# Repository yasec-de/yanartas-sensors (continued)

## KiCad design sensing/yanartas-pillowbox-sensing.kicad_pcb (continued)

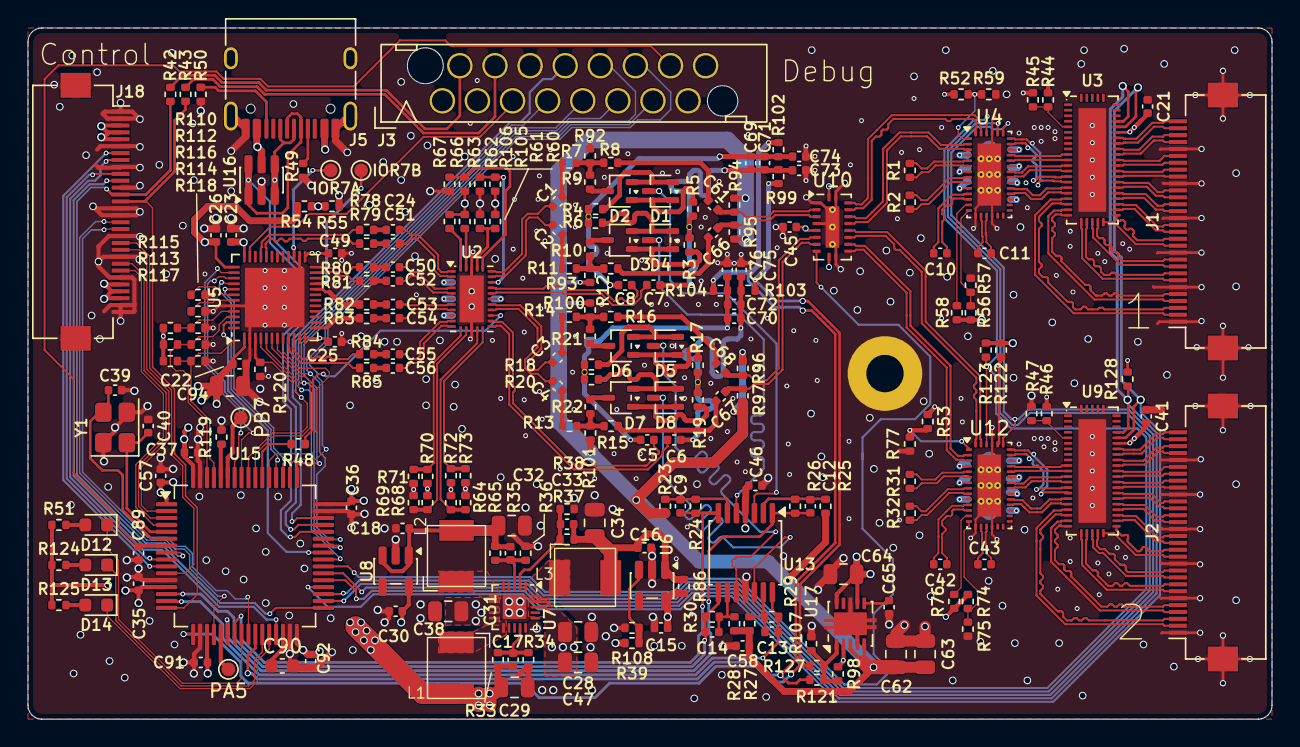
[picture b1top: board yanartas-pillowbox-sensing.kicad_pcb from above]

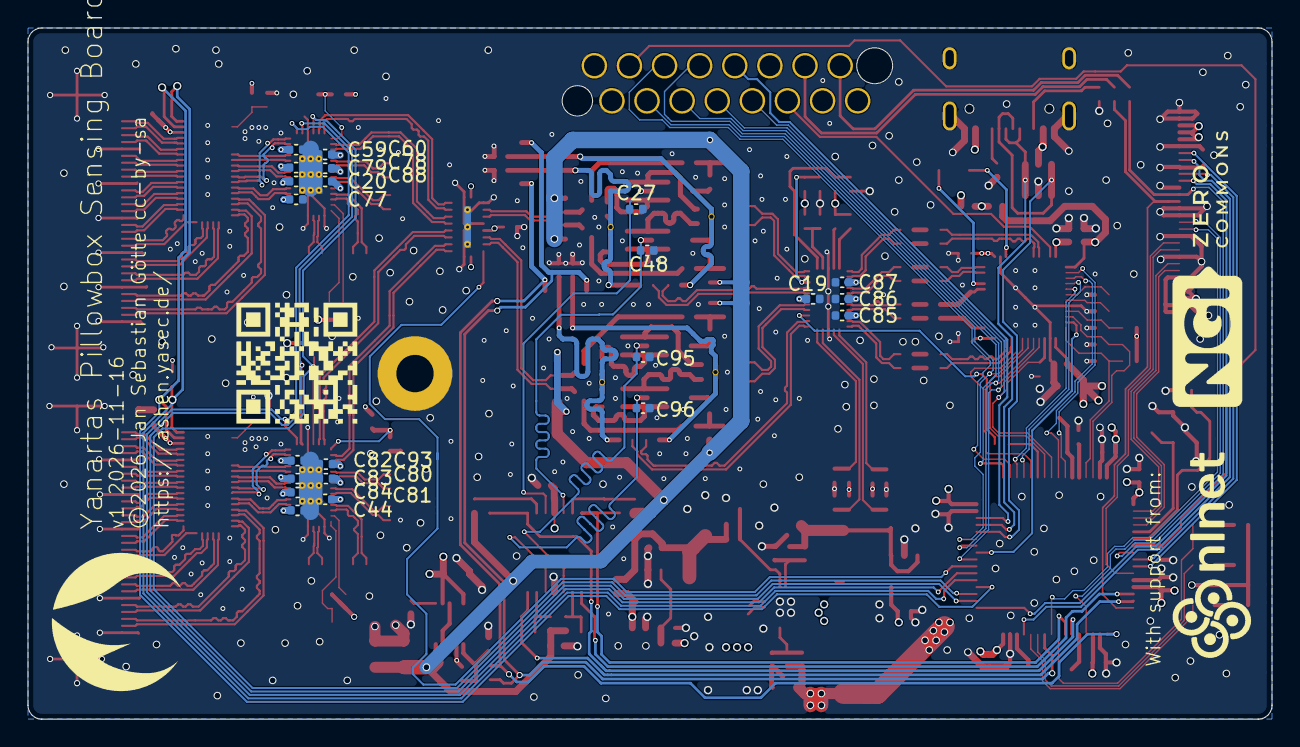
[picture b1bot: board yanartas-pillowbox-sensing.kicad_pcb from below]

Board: 4 copper layers, 90.0 x 50.0 mm, 261 parts (30 on the bottom side), 270 nets.

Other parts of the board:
ashen-logo_w10.00mm: G*****; ashen-logo_w10.00mm
kobee-studio-6AF9AA16: Kobee Studio; kobee-studio-6AF9AA16
ngi-zero-commons-logo_w20.00mm: G*****; ngi-zero-commons-logo_w20.00mm
nlnet-logo_w15.00mm: G*****; nlnet-logo_w15.00mm

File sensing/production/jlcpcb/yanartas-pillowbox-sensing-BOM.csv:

Comment,Designator,Footprint,LCSC Part #
220n,"C1,C2,C3,C4,C5,C6,C7,C8,C10,C11,C24,C42,C43,C50,C51,C52,C53,C54,C55,C56,C61,C65,C66,C67,C68,C71,C72,C73,C74,C75,C76",C_0402_1005Metric,C16772
1u,"C15,C16,C18,C19,C20,C21,C22,C23,C25,C26,C30,C35,C36,C37,C41,C44,C45,C46,C49,C57,C58,C59,C60,C77,C78,C79,C80,C81,C82,C83,C84,C85,C86,C87,C88,C91,C92,C93",C_0402_1005Metric,C52923
22p,"C17,C31,C33",C_0402_1005Metric,C1555
10p,"C27,C39,C40,C48,C95,C96",C_0402_1005Metric,C32949
22u/10V,"C28,C38,C47",C_0805_2012Metric,C45783
22u/6V3,"C29,C32,C34,C62,C63,C64,C94",C_0805_2012Metric,C45783
1n,"C69,C70",C_0402_1005Metric,C1523
100n,C89,C_0402_1005Metric,C1525
4u7/10V,C90,C_0603_1608Metric,C19666
BAT15-04W,"D1,D2,D3,D4,D5,D6,D7,D8",SOT-323_SC-70,C5380972
LED,"D12,D13,D14",LED_0603_1608Metric,C2290
FH12S-30S-0.5SH(55),"J1,J2,J18",Hirose_FH12-30S-0.5SH_1x30-1MP_P0.50mm_Horizontal,C3169607
2u2,"L1,L2,L3",CJIANG_FXL0420,C167206
100,"R1,R2,R31,R32,R42,R43",R_0402_1005Metric,C25076
91,"R3,R4,R5,R6,R17,R18,R19,R20",R_0402_1005Metric,C270574
16,"R7,R8,R9,R10,R11,R12,R13,R14,R15,R16,R21,R22",R_0402_1005Metric,C227309
1k,"R23,R25,R27,R28,R51,R99,R102,R103,R104,R110,R112,R124,R125",R_0402_1005Metric,C11702
3k3,"R24,R26,R29,R30",R_0402_1005Metric,C25890
100k,"R33,R35,R37,R48",R_0402_1005Metric,C25741
22k1,"R34,R39",R_0402_1005Metric,C43473
18k2,R36,R_0402_1005Metric,C25859
49k9,R38,R_0402_1005Metric,C25897
10k,"R44,R46,R56,R58,R59,R74,R76,R77,R92,R93,R94,R95,R96,R97,R100,R101,R108,R119,R121,R127,R128",R_0402_1005Metric,C25744
5k1,"R49,R50",R_0402_1005Metric,C25905
0,R54,R_0402_1005Metric,C17168
4k7,"R66,R69,R73,R105,R106,R113,R115,R117,R120",R_0402_1005Metric,C25900
10,"R78,R79,R80,R81,R82,R83,R84,R85",R_0402_1005Metric,C25077
470k,"R98,R107",R_0402_1005Metric,C25790
3k9,"R122,R123",R_0402_1005Metric,C51721
PI3HDX12311,U2,Diodes_XEA32_X1-QFN-32-1EP_2.85x4.5mm_P0.4mm_EP1.75x3.4mm,C49454029
PI3WVR41310,"U3,U9",Diodes_ZL52_TQFN-52-1EP_3.5x9mm_P0.4mm_EP2x7.5mm,
TMUXHS4446,"U4,U12",Texas_WQFN-40-1EP_3x6mm_P0.4mm_EP1.7x4.5mm_ThermalVias,C35471229
GW1NZ-LV1QN48C6,U5,Gowin_QN48_QFN-48-1EP_6x6mm_P0.4mm_EP4.3x4.3mm,C5799569
TLV74312PDBVR,U6,SOT-23-5,C485149
TMI7003C,U7,QFN-20-1EP_3x3mm_P0.4mm_EP1.7x1.7mm,C840566
TLV74333PDBVR,U8,SOT-23-5,C51953291
TMUXHS4212,U10,Texas_RKS0020A_VQFN-20-1EP_2.5x4.5mm_P0.5mm_EP1x3mm_ThermalVias,C2869871
OPA4354,U13,TSSOP-14_4.4x5mm_P0.65mm,C527494
STM32U575RGTx,U15,LQFP-64_10x10mm_P0.5mm,C5270980
USBLC6-4SC6,U16,SOT-23-6,C558419
TPS51200DRC,U17,VSON-10-1EP_3x3mm_P0.5mm_EP1.65x2.4mm,C34771
16MHz 10p,Y1,Crystal_SMD_3225-4Pin_3.2x2.5mm,C13738

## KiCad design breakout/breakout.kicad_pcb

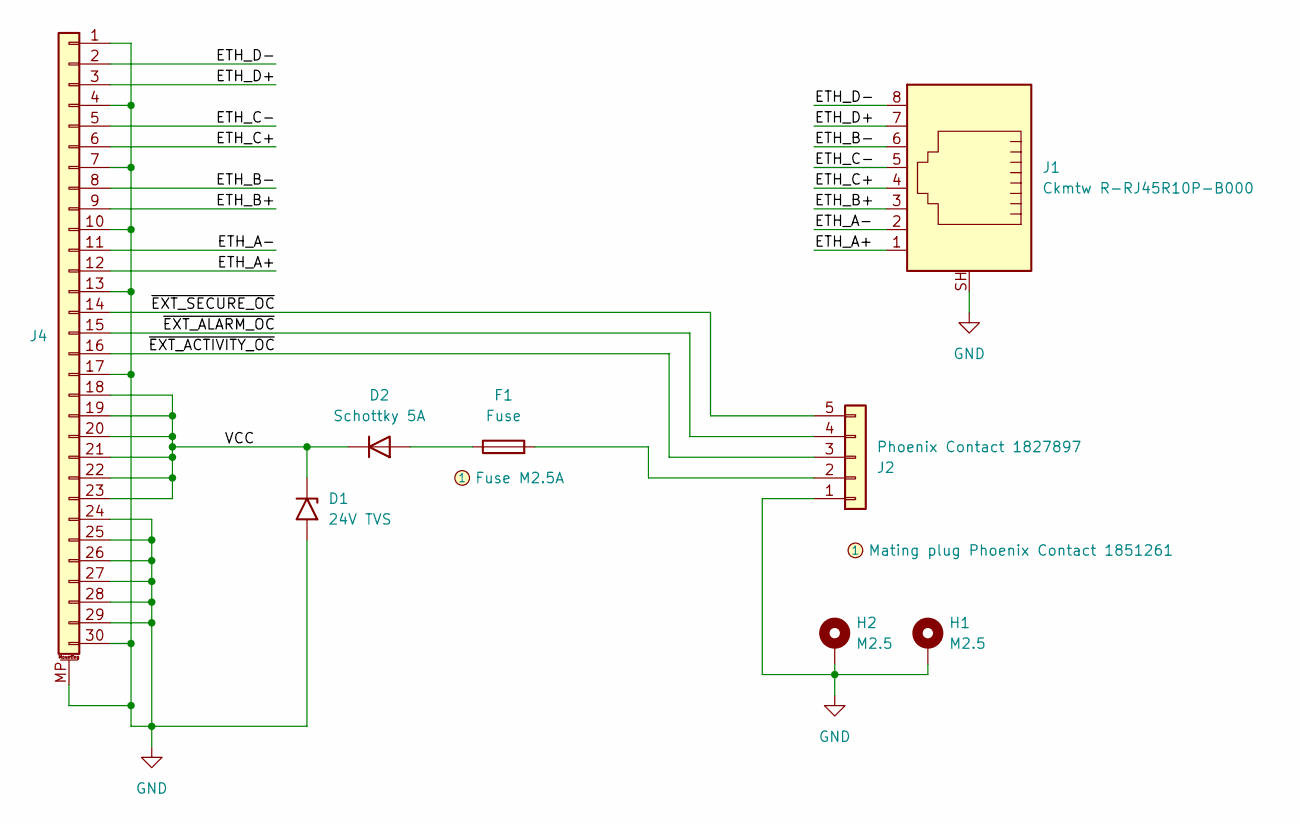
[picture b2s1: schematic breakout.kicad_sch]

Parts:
D1: 24V TVS; D_DO-27_P15.24mm_Horizontal; LCSC C5350009
D2: Schottky 5A; D_DO-27_P15.24mm_Horizontal; LCSC C154825
F1: Fuse; Fuseholder_Clip-5x20mm_Littelfuse_520_Inline_P20.50x5.80mm_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; LCSC C142924
H1, H2: M2.5; MountingHole_2.7mm_M2.5_DIN965_Pad_TopBottom
J1: Ckmtw R-RJ45R10P-B000; RJ45_Ninigi_GE; LCSC C386758
J2: Phoenix Contact 1827897; PhoenixContact_MC_1,5_5-GF-3.81_1x05_P3.81mm_Horizontal_Thr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; LCSC C3579871
J4: FH12S-30S-0.5SH(55); Hirose_FH12-30S-0.5SH_1x30-1MP_P0.50mm_Horizontal; LCSC C3169607

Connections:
/ETH_A+: J1.1, J4.12
/ETH_A-: J1.2, J4.11
/ETH_B+: J1.3, J4.9
/ETH_B-: J1.6, J4.8
/ETH_C+: J1.4, J4.6
/ETH_C-: J1.5, J4.5
/ETH_D+: J1.7, J4.3
/ETH_D-: J1.8, J4.2
/VCC: D1.1 (A1), D2.1 (K), J4.18, J4.19, J4.20, J4.21, J4.22, J4.23
/~EXT_ACTIVITY_OC: J2.3, J4.16
/~EXT_ALARM_OC: J2.4, J4.15
/~EXT_SECURE_OC: J2.5, J4.14
GND: D1.2 (A2), H1.1 (1_1), H2.1 (1_1), J1.SH, J2.1, J4.1, J4.4, J4.7, J4.10, J4.13, J4.17, J4.24, J4.25, J4.26, J4.27, J4.28, J4.29, J4.30, J4.MP (MountPin)
unnamed: D2.2 (A), F1.1
unnamed: F1.2, J2.2

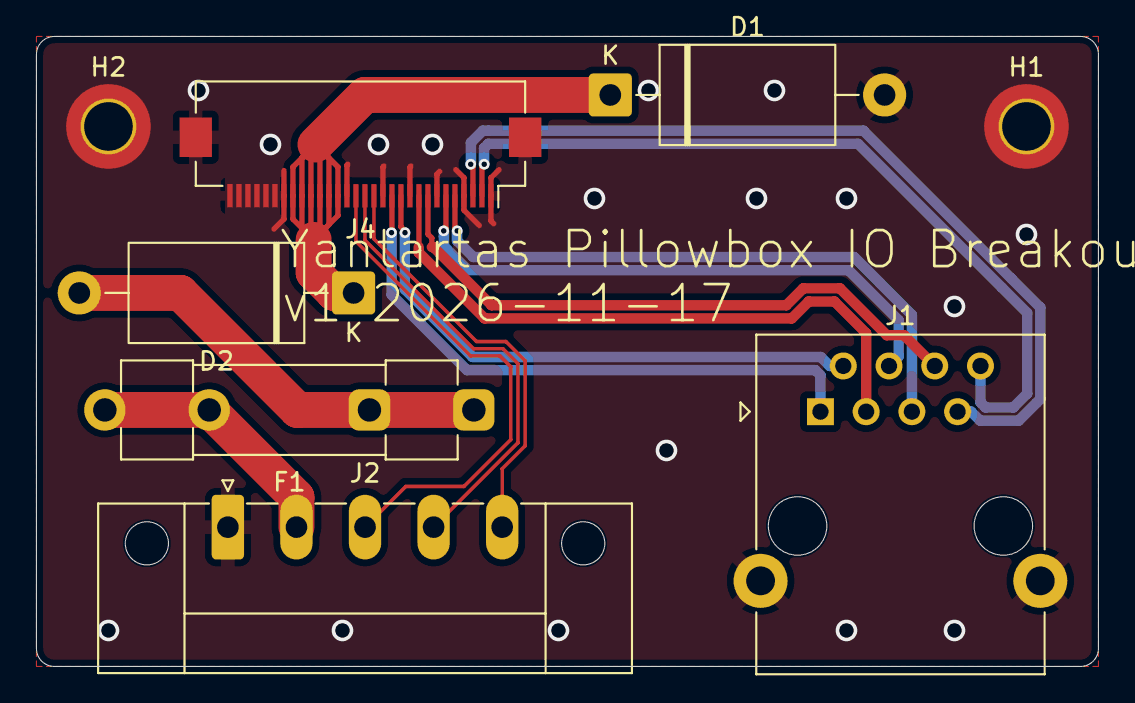
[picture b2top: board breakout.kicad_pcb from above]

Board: 2 copper layers, 59.0 x 35.0 mm, 8 parts (0 on the bottom side), 15 nets.

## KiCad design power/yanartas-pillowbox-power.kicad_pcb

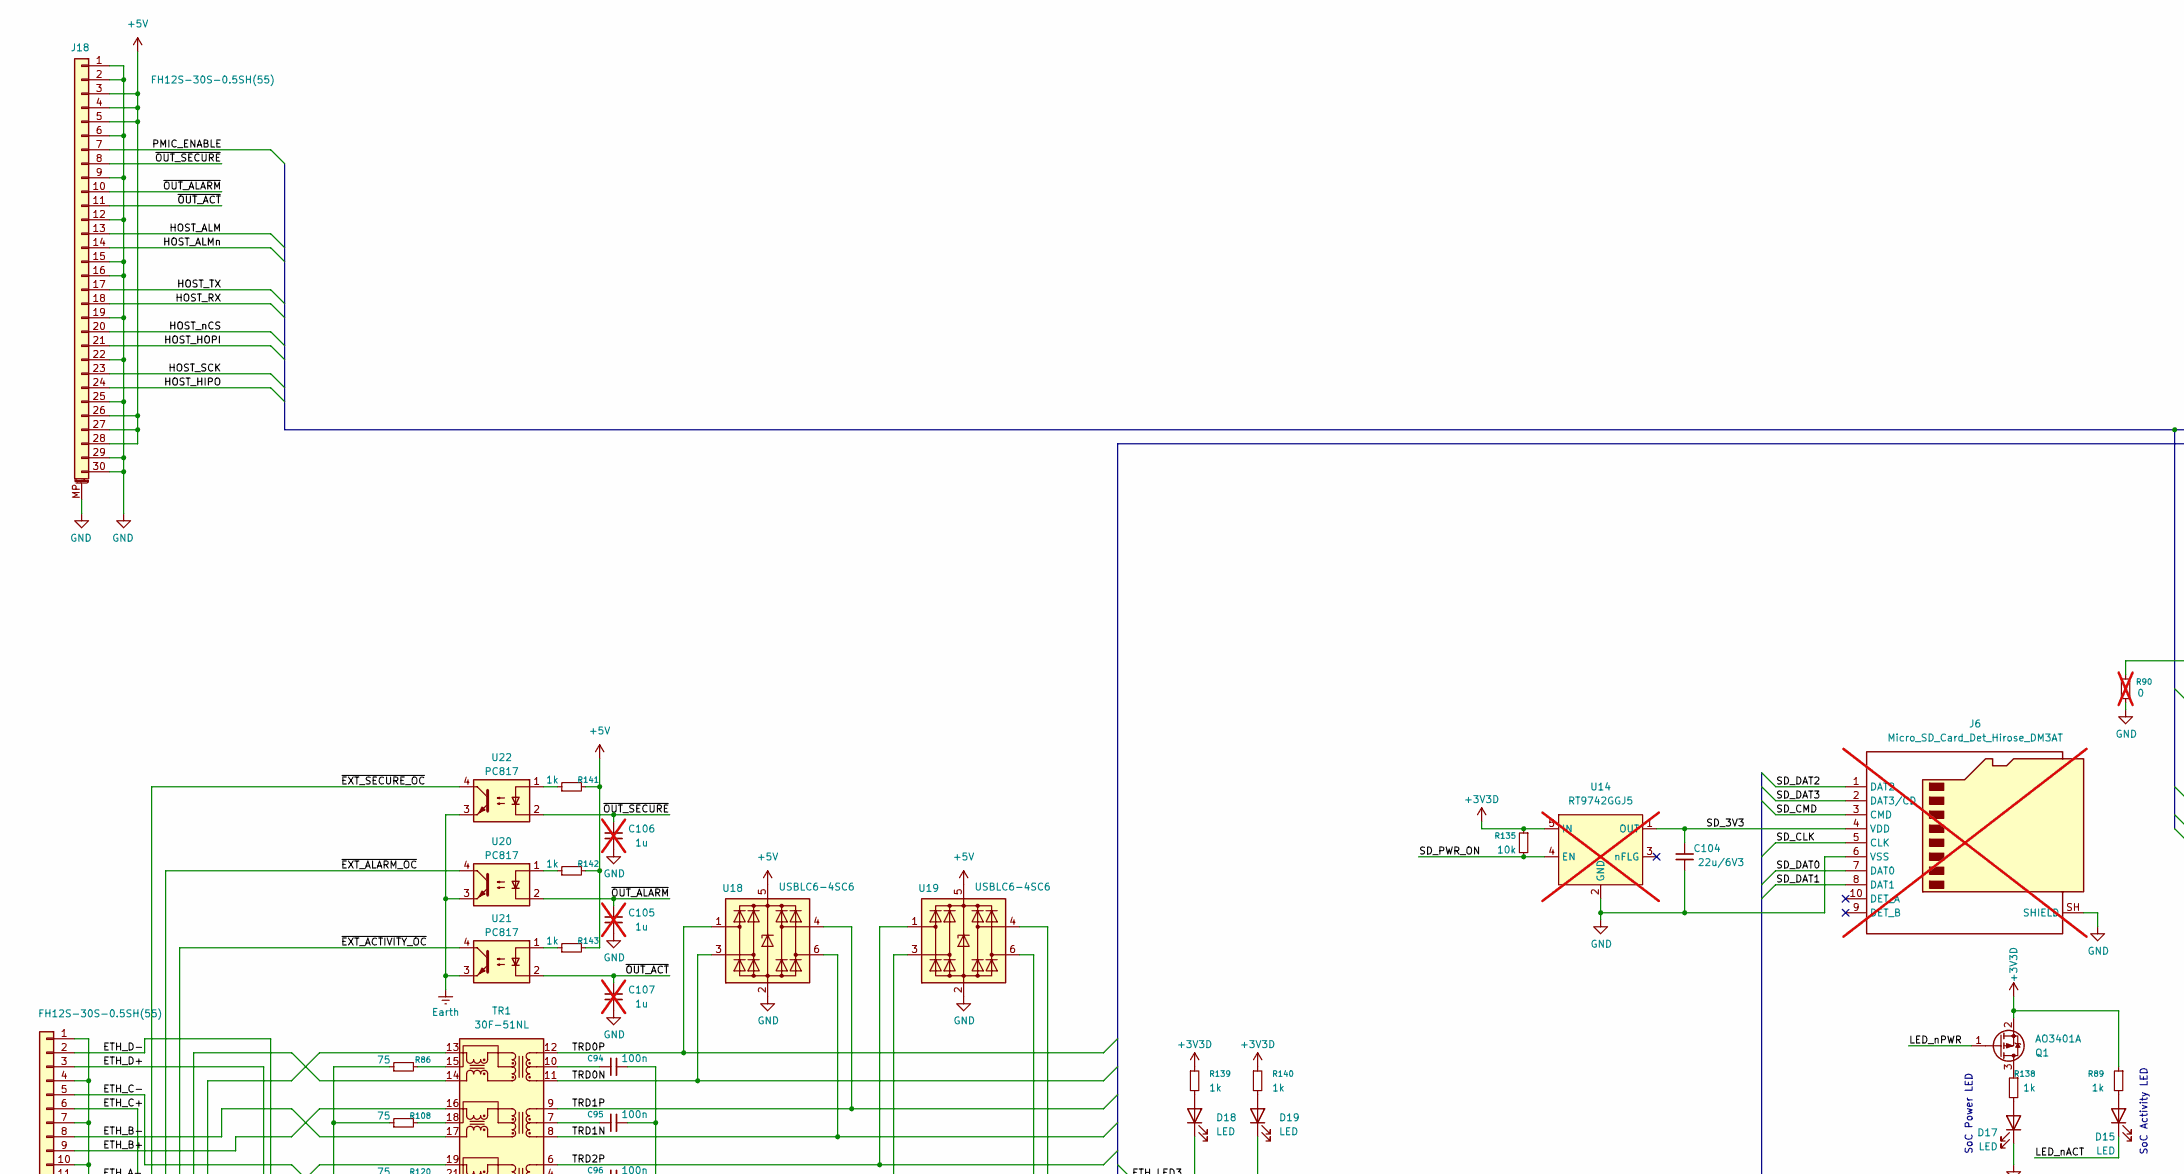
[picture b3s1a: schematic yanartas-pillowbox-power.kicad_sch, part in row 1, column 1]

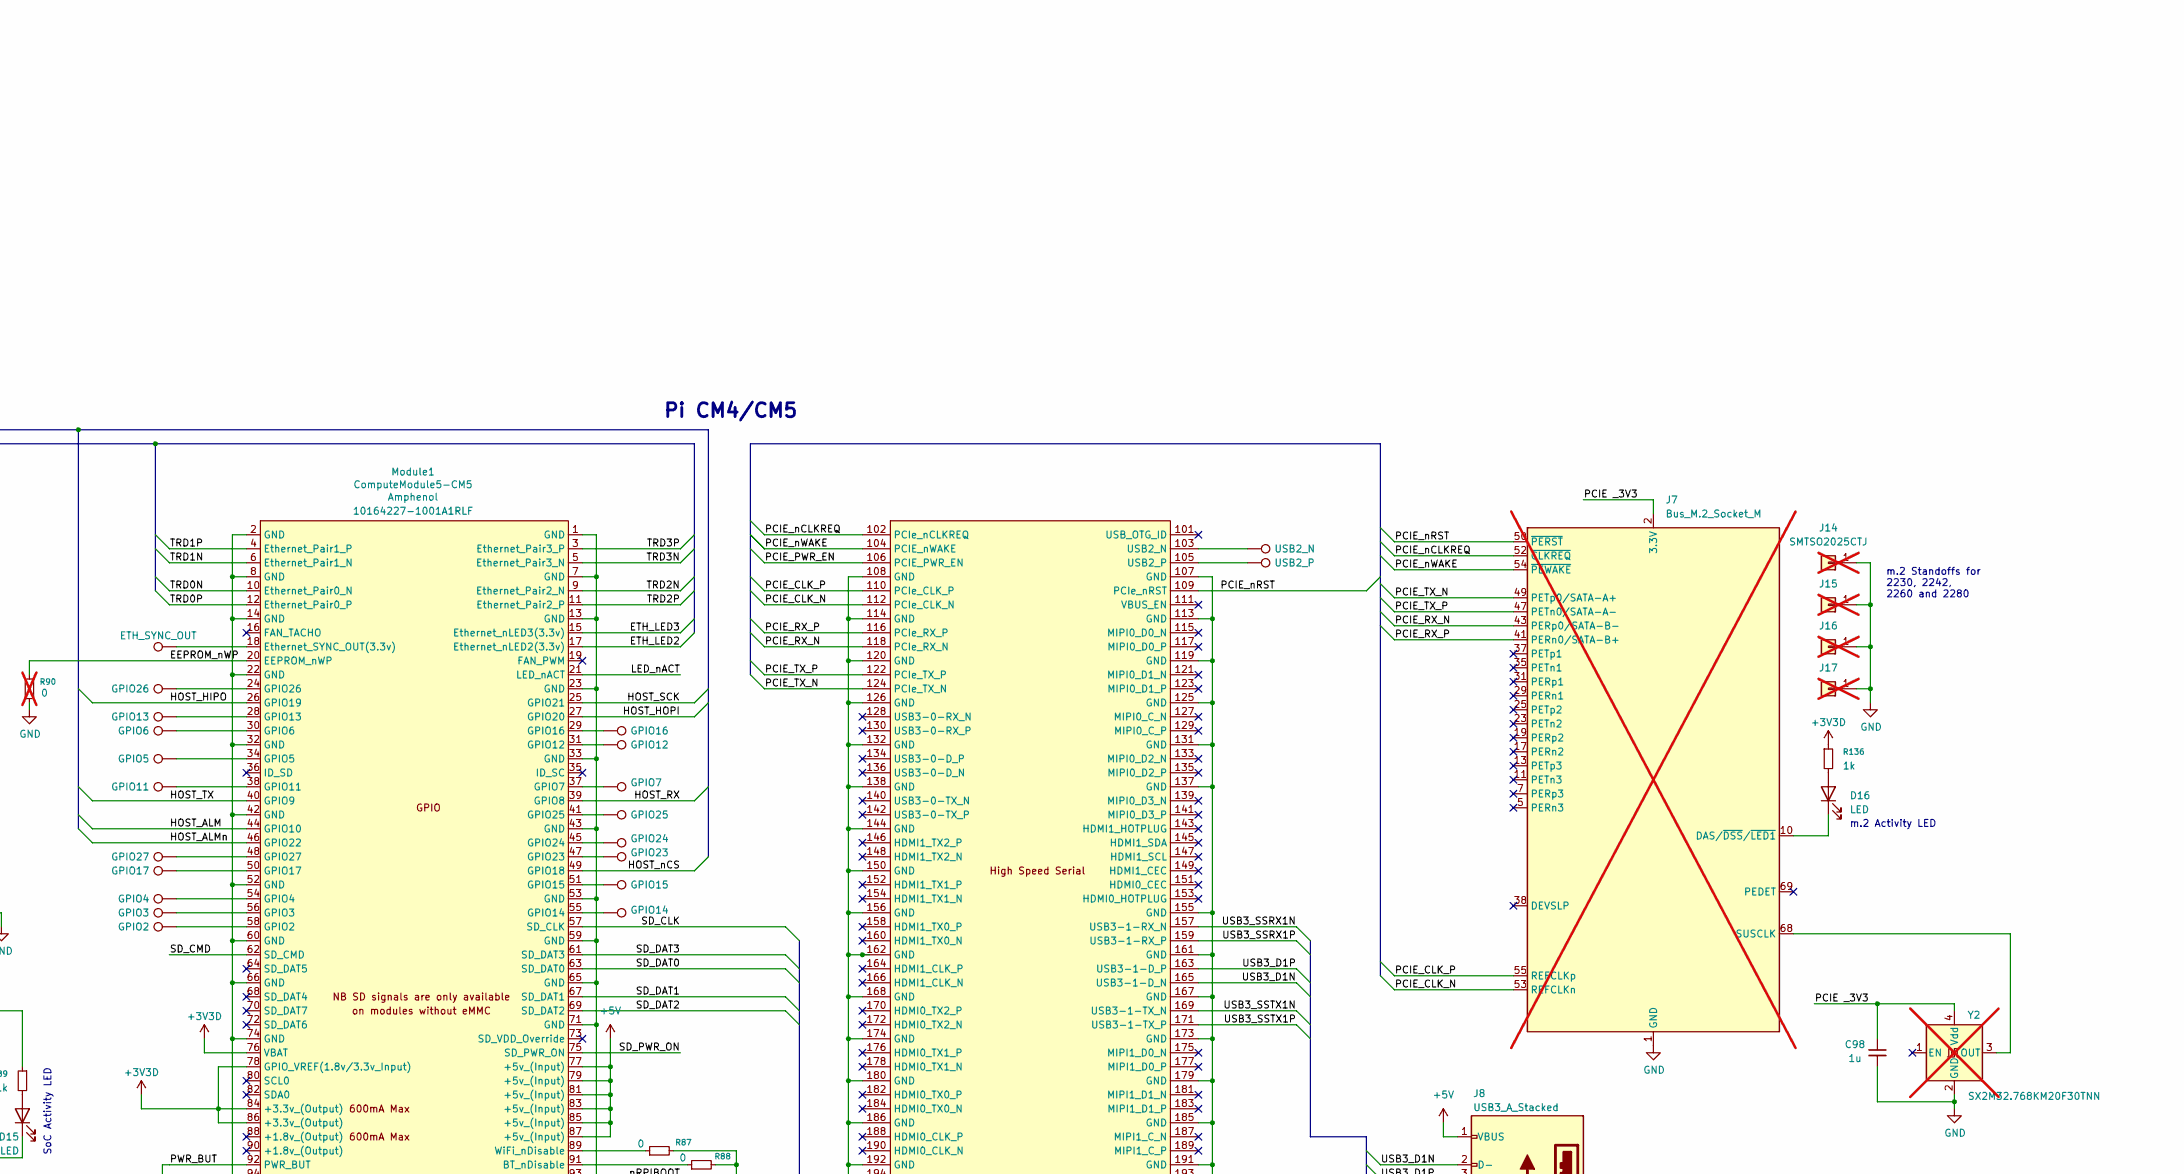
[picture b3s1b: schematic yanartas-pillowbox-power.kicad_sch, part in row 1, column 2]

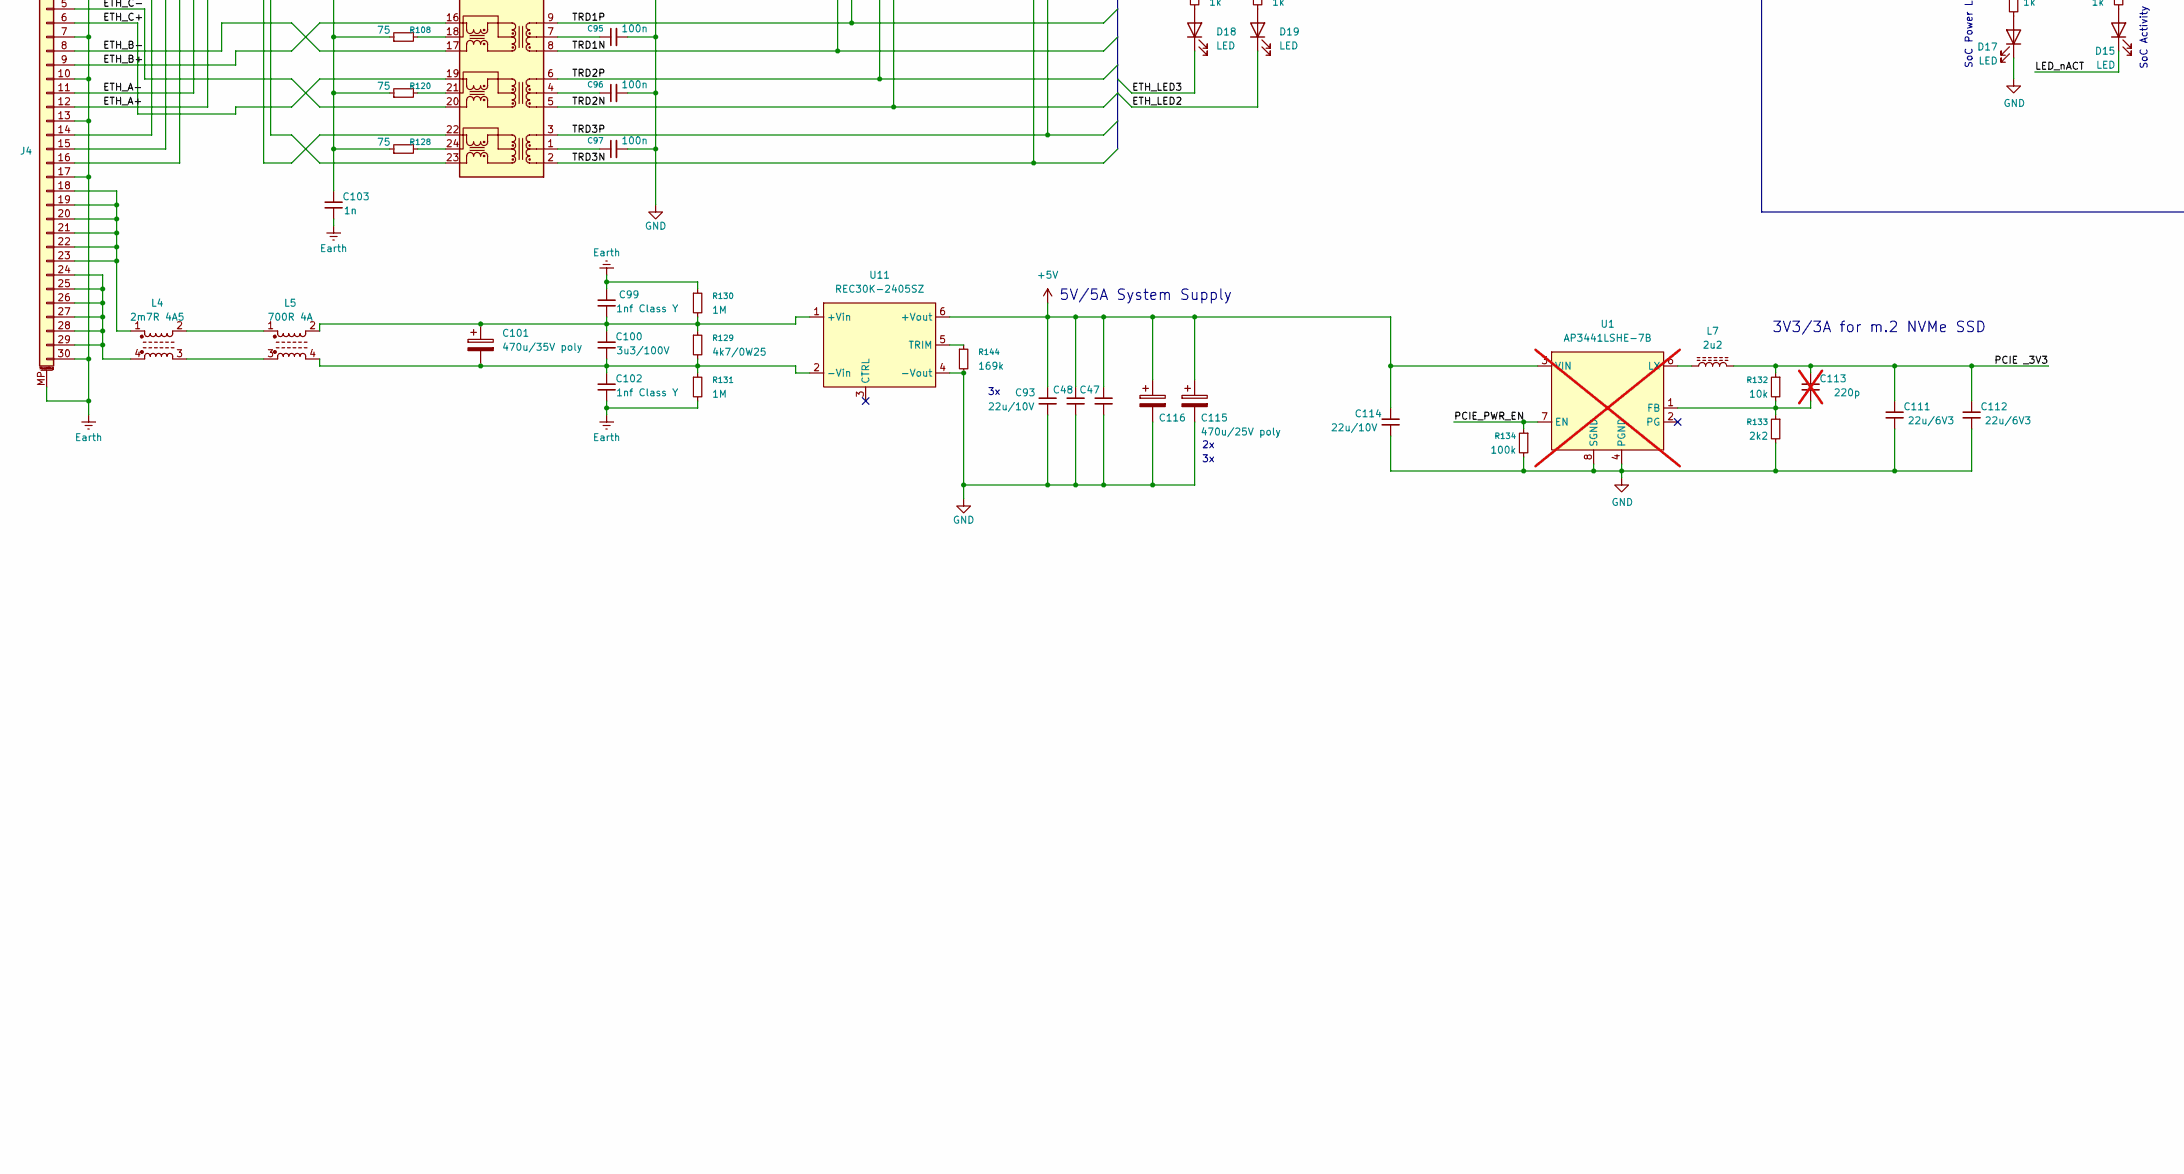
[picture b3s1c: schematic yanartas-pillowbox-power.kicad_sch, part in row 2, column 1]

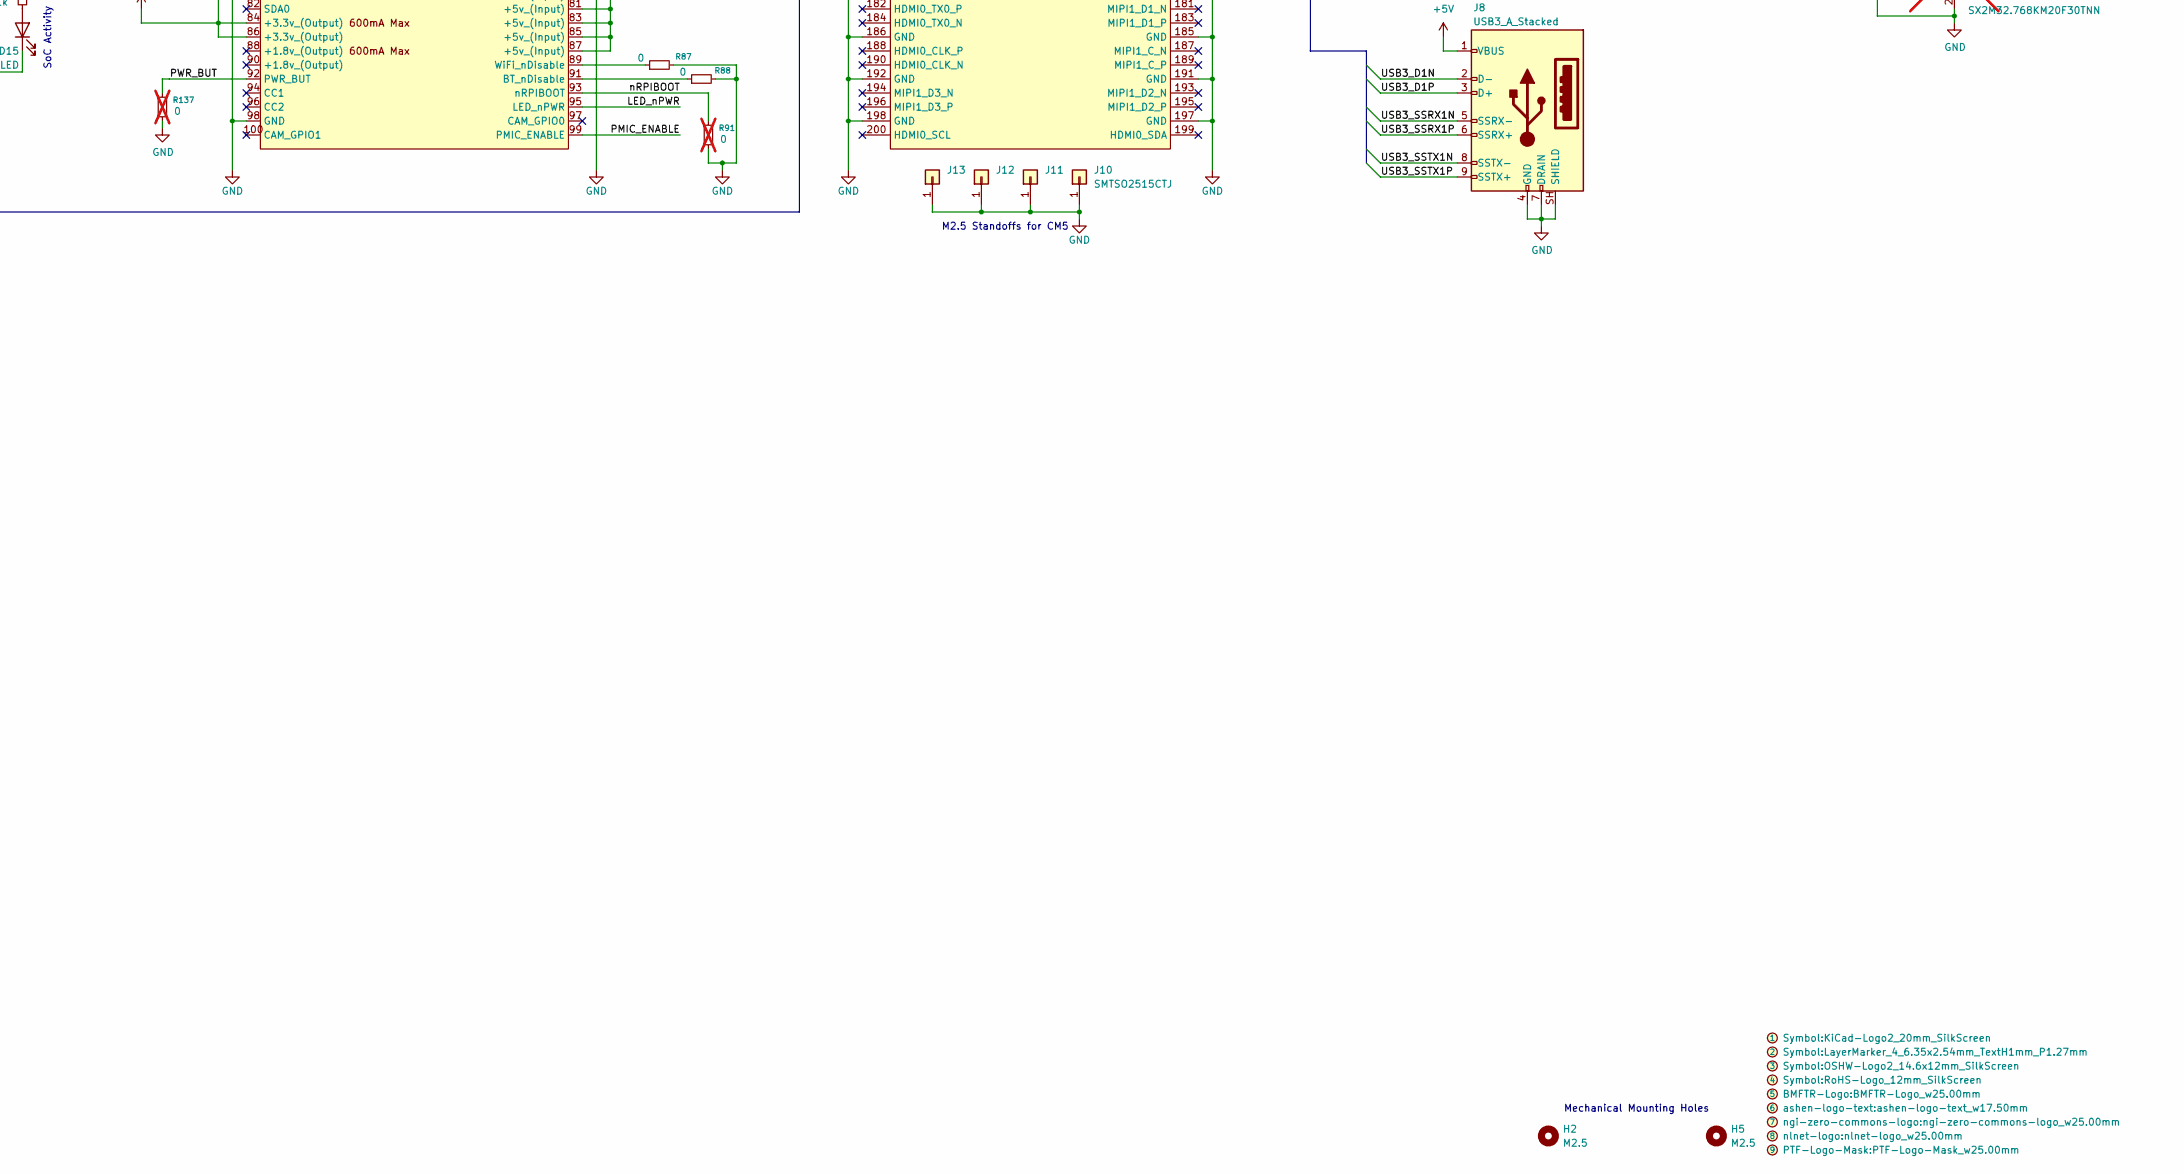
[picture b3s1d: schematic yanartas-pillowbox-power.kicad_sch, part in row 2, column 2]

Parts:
C47, C48, C93, C114: 22u/10V; C_0805_2012Metric; LCSC C45783
C94, C95, C96, C97: 100n; C_0402_1005Metric; LCSC C1525
C98: 1u; C_0402_1005Metric; LCSC C52923
C99, C102: 1nf Class Y; C_Rect_L13.0mm_W4.0mm_P10.00mm_FKS3_FKP3_MKS4; LCSC C361361
C100: 3u3/100V; C_1206_3216Metric; LCSC C695361
C101: 470u/35V poly; CP_Radial_D10.0mm_P5.00mm; MfgPN A750MV477M1VAAE018; LCSC C1020051
C103: 1n; C_0603_1608Metric; LCSC C1588
C104, C111, C112: 22u/6V3; C_0805_2012Metric; LCSC C45783
C105, C106, C107: 1u; C_0402_1005Metric; LCSC C52923; not fitted
C113: 220p; C_0402_1005Metric; not fitted
C115, C116: 470u/25V poly; CP_Radial_D10.0mm_P5.00mm; MfgPN A750MS477M1EAAE015; LCSC C696345
D15, D16, D17, D18, D19: LED; LED_0603_1608Metric; LCSC C2290
H2, H5: M2.5; MountingHole_2.7mm_M2.5; LCSC NA
J4, J18: FH12S-30S-0.5SH(55); Hirose_FH12-30S-0.5SH_1x30-1MP_P0.50mm_Horizontal; LCSC C3169607
J6: Micro_SD_Card_Det_Hirose_DM3AT; microSD_HC_Hirose_DM3AT-SF-PEJM5; MPN DM3AT-SF-PEJM5; LCSC C114218; not fitted
J7: Bus_M.2_Socket_M; CONN-SMD_MDT420M02001; LCSC C2927698; not fitted
J8: USB3_A_Stacked; USB_A_Receptacle_XKB_U231-091N-4BLRA00-S; LCSC C2880618
J10, J11, J12, J13: SMTSO2515CTJ; SINHOO_SMTSO25XX; LCSC C2915629
J14, J15, J16, J17: SMTSO2025CTJ; SINHOO_SMTSO20XX; LCSC C2916321; not fitted
L4: 2m7R 4A5; EPCOS_B82723A; MPN B82723A2402N001; LCSC NA
L5: 700R 4A; TDK_ACM7060; MPN ACM7060-701-2PL-TL01; LCSC C78246
L7: 2u2; CJIANG_FXL0420; LCSC C167206
Module1: ComputeModule5-CM5; Raspberry-Pi-5-Compute-Module-A; Part Description 100 Position Connector Receptacle, Cent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; LCSC C6782225
Module2: ComputeModule5-CM5; Raspberry-Pi-5-Compute-Module-B; Part Description 100 Position Connector Receptacle, Cent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; LCSC C6782225
Q1: AO3401A; SOT-23; LCSC C15127
R86, R108, R120, R128: 75; R_0402_1005Metric; LCSC C25133
R87, R88: 0; R_0402_1005Metric; LCSC C17168
R89, R136, R138, R139, R140, R141, R142, R143: 1k; R_0402_1005Metric; LCSC C11702
R90, R91, R137: 0; R_0402_1005Metric; LCSC C17168; not fitted
R129: 4k7/0W25; R_1206_3216Metric; LCSC C17936
R130, R131: 1M; R_0603_1608Metric; LCSC C22935
R132, R135: 10k; R_0402_1005Metric; LCSC C25744
R133: 2k2; R_0402_1005Metric; LCSC C25879
R134: 100k; R_0402_1005Metric; LCSC C25741
R144: 169k; R_0603_1608Metric; LCSC C22817
TP1: GPIO27; TestPoint_Pad_D1.0mm; LCSC NA
TP2: GPIO17; TestPoint_Pad_D1.0mm; LCSC NA
TP3: GPIO4; TestPoint_Pad_D1.0mm; LCSC NA
TP4: GPIO3; TestPoint_Pad_D1.0mm; LCSC NA
TP5: GPIO2; TestPoint_Pad_D1.0mm; LCSC NA
TP6: GPIO11; TestPoint_Pad_D1.0mm; LCSC NA
TP7: GPIO5; TestPoint_Pad_D1.0mm; LCSC NA
TP8: GPIO6; TestPoint_Pad_D1.0mm; LCSC NA
TP9: GPIO13; TestPoint_Pad_D1.0mm; LCSC NA
TP10: GPIO26; TestPoint_Pad_D1.0mm; LCSC NA
TP11: ETH_SYNC_OUT; TestPoint_Pad_D1.0mm; LCSC NA
TP12: GPIO14; TestPoint_Pad_D1.0mm; LCSC NA
TP13: GPIO15; TestPoint_Pad_D1.0mm; LCSC NA
TP14: GPIO23; TestPoint_Pad_D1.0mm; LCSC NA
TP15: GPIO24; TestPoint_Pad_D1.0mm; LCSC NA
TP16: GPIO25; TestPoint_Pad_D1.0mm; LCSC NA
TP17: GPIO7; TestPoint_Pad_D1.0mm; LCSC NA
TP18: GPIO12; TestPoint_Pad_D1.0mm; LCSC NA
TP19: GPIO16; TestPoint_Pad_D1.0mm; LCSC NA
TP20: USB2_N; TestPoint_Pad_D1.0mm; LCSC NA
TP21: USB2_P; TestPoint_Pad_D1.0mm; LCSC NA
TR1: 30F-51NL; Transformer_Ethernet_YDS_30F-51NL_SO-24_7.1x15.1mm; LCSC C123168
U1: AP3441LSHE-7B; DFN-8-1EP_2x2mm_P0.5mm_EP1.05x1.75mm; LCSC C2072094; not fitted
U11: REC30K-2405SZ; RECOM_REC30K-2405SZ; LCSC NA
U14: RT9742GGJ5; SOT-23-5; Part Description Power Switch/Driver 1:1 N-Channel 1A TS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; LCSC C250547; not fitted
U18, U19: USBLC6-4SC6; SOT-23-6; LCSC C558419
U20, U21, U22: PC817; SMDIP-4_W7.62mm; LCSC C41807
Y2: SX2M32.768KM20F30TNN; Crystal_SMD_2520-4Pin_2.5x2.0mm; LCSC C2901603; not fitted

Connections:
+3V3D: Module1.76 (VBAT), Module1.78 (GPIO_VREF(1.8v/3.3v_Input)), Module1.84 (+3.3v_(Output)), Module1.86 (+3.3v_(Output)), Q1.2 (S), R89.1, R135.1, R136.1, R139.1, R140.1, U14.5 (IN)
+5V: C47.2, C48.2, C93.2, C114.2, C115.1, C116.1, J8.1 (VBUS), J18.3, J18.4, J18.5, J18.26, J18.27, J18.28, Module1.77 (+5v_(Input)), Module1.79 (+5v_(Input)), Module1.81 (+5v_(Input)), Module1.83 (+5v_(Input)), Module1.85 (+5v_(Input)), Module1.87 (+5v_(Input)), R141.2, R142.2, R143.2, U1.3 (VIN), U11.6 (+Vout), U18.5 (VBUS), U19.5 (VBUS)
/EEPROM_nWP: Module1.20 (EEPROM_nWP), R90.2
/ETH_A+: J4.12, TR1.13 (MX4-)
/ETH_A-: J4.11, TR1.14 (MX4+)
/ETH_B+: J4.9, TR1.16 (MX3-)
/ETH_B-: J4.8, TR1.17 (MX3+)
/ETH_C+: J4.6, TR1.19 (MX2-)
/ETH_C-: J4.5, TR1.20 (MX2+)
/ETH_D+: J4.3, TR1.22 (MX1-)
/ETH_D-: J4.2, TR1.23 (MX1+)
/ETH_LED2: D19.1 (K), Module1.17 (Ethernet_nLED2(3.3v))
/ETH_LED3: D18.1 (K), Module1.15 (Ethernet_nLED3(3.3v))
/HOST_ALM: J18.13, Module1.44 (GPIO10)
/HOST_ALMn: J18.14, Module1.46 (GPIO22)
/HOST_HIPO: J18.24, Module1.26 (GPIO19)
/HOST_HOPI: J18.21, Module1.27 (GPIO20)
/HOST_RX: J18.18, Module1.39 (GPIO8)
/HOST_SCK: J18.23, Module1.25 (GPIO21)
/HOST_TX: J18.17, Module1.40 (GPIO9)
/HOST_nCS: J18.20, Module1.49 (GPIO18)
/LED_nACT: D15.1 (K), Module1.21 (LED_nACT)
/LED_nPWR: Module1.95 (LED_nPWR), Q1.1 (G)
/PCIE _3V3: C98.2, C111.2, C112.2, C113.2, J7.2 (3.3V), J7.4 (3.3V), J7.12 (3.3V), J7.14 (3.3V), J7.16 (3.3V), J7.18 (3.3V), J7.70 (3.3V), J7.72 (3.3V), J7.74 (3.3V), L7.2, R132.1, Y2.4 (Vdd)
/PCIE_CLK_N: J7.53 (REFCLKn), Module2.112 (PCIe_CLK_N)
/PCIE_CLK_P: J7.55 (REFCLKp), Module2.110 (PCIe_CLK_P)
/PCIE_PWR_EN: Module2.106 (PCIE_PWR_EN), R134.1, U1.7 (EN)
/PCIE_RX_N: J7.43 (PERp0/SATA-B-), Module2.118 (PCIe_RX_N)
/PCIE_RX_P: J7.41 (PERn0/SATA-B+), Module2.116 (PCIe_RX_P)
/PCIE_TX_N: J7.49 (PETp0/SATA-A+), Module2.124 (PCIe_TX_N)
/PCIE_TX_P: J7.47 (PETn0/SATA-A-), Module2.122 (PCIe_TX_P)
/PCIE_nCLKREQ: J7.52 (~CLKREQ), Module2.102 (PCIe_nCLKREQ)
/PCIE_nRST: J7.50 (~PERST), Module2.109 (PCIe_nRST)
/PCIE_nWAKE: J7.54 (~PEWAKE), Module2.104 (PCIE_nWAKE)
/PMIC_ENABLE: J18.7, Module1.99 (PMIC_ENABLE)
/PWR_BUT: Module1.92 (PWR_BUT), R137.2
/SD_3V3: C104.2, J6.4 (VDD), U14.1 (OUT)
/SD_CLK: J6.5 (CLK), Module1.57 (SD_CLK)
/SD_CMD: J6.3 (CMD), Module1.62 (SD_CMD)
/SD_DAT0: J6.7 (DAT0), Module1.63 (SD_DAT0)
/SD_DAT1: J6.8 (DAT1), Module1.67 (SD_DAT1)
/SD_DAT2: J6.1 (DAT2), Module1.69 (SD_DAT2)
/SD_DAT3: J6.2 (DAT3/CD), Module1.61 (SD_DAT3)
/SD_PWR_ON: Module1.75 (SD_PWR_ON), R135.2, U14.4 (EN)
/TRD0N: Module1.10 (Ethernet_Pair0_N), TR1.11 (TD4+), U18.3 (I/O2)
/TRD0P: Module1.12 (Ethernet_Pair0_P), TR1.12 (TD4-), U18.1 (I/O1)
/TRD1N: Module1.6 (Ethernet_Pair1_N), TR1.8 (TD3+), U18.6 (I/O4)
/TRD1P: Module1.4 (Ethernet_Pair1_P), TR1.9 (TD3-), U18.4 (I/O3)
/TRD2N: Module1.9 (Ethernet_Pair2_N), TR1.5 (TD2+), U19.3 (I/O2)
/TRD2P: Module1.11 (Ethernet_Pair2_P), TR1.6 (TD2-), U19.1 (I/O1)
/TRD3N: Module1.5 (Ethernet_Pair3_N), TR1.2 (TD1+), U19.6 (I/O4)
/TRD3P: Module1.3 (Ethernet_Pair3_P), TR1.3 (TD1-), U19.4 (I/O3)
/USB3_D1N: J8.2 (D-), Module2.165 (USB3-1-D_N)
/USB3_D1P: J8.3 (D+), Module2.163 (USB3-1-D_P)
/USB3_SSRX1N: J8.5 (SSRX-), Module2.157 (USB3-1-RX_N)
/USB3_SSRX1P: J8.6 (SSRX+), Module2.159 (USB3-1-RX_P)
/USB3_SSTX1N: J8.8 (SSTX-), Module2.169 (USB3-1-TX_N)
/USB3_SSTX1P: J8.9 (SSTX+), Module2.171 (USB3-1-TX_P)
/nRPIBOOT: Module1.93 (nRPIBOOT), R91.2
/~EXT_ACTIVITY_OC: J4.16, U21.4
/~EXT_ALARM_OC: J4.15, U20.4
/~EXT_SECURE_OC: J4.14, U22.4
/~OUT_ACT: C107.2, J18.11, U21.2
/~OUT_ALARM: C105.2, J18.10, U20.2
/~OUT_SECURE: C106.2, J18.8, U22.2
Earth: C99.2, C102.1, C103.1, J4.1, J4.4, J4.7, J4.10, J4.13, J4.17, J4.30, J4.MP (MountPin), R130.1, R131.2, U20.3, U21.3, U22.3
GND: C47.1, C48.1, C93.1, C94.2, C95.2, C96.2, C97.2, C98.1, C104.1, C105.1, C106.1, C107.1, C111.1, C112.1, C114.1, C115.2, C116.2, D17.1 (K), J6.6 (VSS), J6.SH (SHIELD), J7.1 (GND), J7.3 (GND), J7.9 (GND), J7.15 (GND), J7.21 (GND), J7.27 (GND), J7.33 (GND), J7.39 (GND), J7.45 (GND), J7.51 (GND), J7.57 (GND), J7.71 (GND), J7.73 (GND), J7.75 (GND), J8.4 (GND), J8.7 (DRAIN), J8.SH (SHIELD), J10.1 (Pin_1_1), J11.1 (Pin_1_1), J12.1 (Pin_1_1), J13.1 (Pin_1_1), J14.1 (Pin_1_1), J15.1 (Pin_1_1), J16.1 (Pin_1_1), J17.1 (Pin_1_1), J18.1, J18.2, J18.6, J18.9, J18.12, J18.15, J18.16, J18.19, J18.22, J18.25, J18.29, J18.30, J18.MP (MountPin), Module1.1 (GND), Module1.2 (GND), Module1.7 (GND), Module1.8 (GND), Module1.13 (GND), Module1.14 (GND), Module1.22 (GND), Module1.23 (GND), Module1.32 (GND), Module1.33 (GND), Module1.42 (GND), Module1.43 (GND), Module1.52 (GND), Module1.53 (GND), Module1.59 (GND), Module1.60 (GND), Module1.65 (GND), Module1.66 (GND), Module1.71 (GND), Module1.74 (GND), Module1.98 (GND), Module2.107 (GND), Module2.108 (GND), Module2.113 (GND), Module2.114 (GND), Module2.119 (GND), Module2.120 (GND), Module2.125 (GND), Module2.126 (GND), Module2.131 (GND), Module2.132 (GND), Module2.137 (GND), Module2.138 (GND), Module2.144 (GND), Module2.150 (GND), Module2.155 (GND), Module2.156 (GND), Module2.161 (GND), Module2.162 (GND), Module2.167 (GND), Module2.168 (GND), Module2.173 (GND), Module2.174 (GND), Module2.179 (GND), Module2.180 (GND), Module2.185 (GND), Module2.186 (GND), Module2.191 (GND), Module2.192 (GND), Module2.197 (GND), Module2.198 (GND), R87.2, R88.2, R90.1, R91.1, R133.2, R134.2, R137.1, R144.2, U1.4 (PGND), U1.8 (SGND), U1.9 (PAD), U11.4 (-Vout), U14.2 (GND), U18.2 (GND), U19.2 (GND), Y2.2 (GND)
unnamed: C94.1, TR1.10 (CT)
unnamed: C95.1, TR1.7 (CT)
unnamed: C96.1, TR1.4 (CT)
unnamed: C97.1, TR1.1 (CT)
unnamed: C103.2, R86.1, R108.1, R120.1, R128.1
unnamed: D15.2 (A), R89.2
unnamed: D16.2 (A), R136.2
unnamed: D16.1 (K), J7.10 (DAS/~DSS/~LED1)
unnamed: D17.2 (A), R138.2
unnamed: D18.2 (A), R139.2
unnamed: D19.2 (A), R140.2
unnamed: J4.18, J4.19, J4.20, J4.21, J4.22, J4.23, L4.1
unnamed: J4.24, J4.25, J4.26, J4.27, J4.28, J4.29, L4.4
unnamed: J7.68 (SUSCLK), Y2.3 (OUT)
unnamed: L4.2, L5.1
unnamed: L4.3, L5.3
unnamed: Module1.91 (BT_nDisable), R88.1
unnamed: Module1.18 (Ethernet_SYNC_OUT(3.3v)), TP11.1 (1_1)
unnamed: Module1.58 (GPIO2), TP5.1 (1_1)
unnamed: Module1.56 (GPIO3), TP4.1 (1_1)
unnamed: Module1.54 (GPIO4), TP3.1 (1_1)
unnamed: Module1.34 (GPIO5), TP7.1 (1_1)
unnamed: Module1.30 (GPIO6), TP8.1 (1_1)
unnamed: Module1.37 (GPIO7), TP17.1 (1_1)
unnamed: Module1.38 (GPIO11), TP6.1 (1_1)
unnamed: Module1.31 (GPIO12), TP18.1 (1_1)
unnamed: Module1.28 (GPIO13), TP9.1 (1_1)
unnamed: Module1.55 (GPIO14), TP12.1 (1_1)
unnamed: Module1.51 (GPIO15), TP13.1 (1_1)
unnamed: Module1.29 (GPIO16), TP19.1 (1_1)
unnamed: Module1.50 (GPIO17), TP2.1 (1_1)
unnamed: Module1.47 (GPIO23), TP14.1 (1_1)
unnamed: Module1.45 (GPIO24), TP15.1 (1_1)
unnamed: Module1.41 (GPIO25), TP16.1 (1_1)
unnamed: Module1.24 (GPIO26), TP10.1 (1_1)
unnamed: Module1.48 (GPIO27), TP1.1 (1_1)
unnamed: Module1.89 (WiFi_nDisable), R87.1
unnamed: Module2.103 (USB2_N), TP20.1 (1_1)
unnamed: Module2.105 (USB2_P), TP21.1 (1_1)
unnamed: Q1.3 (D), R138.1
unnamed: R86.2, TR1.15 (CT)
unnamed: R108.2, TR1.18 (CT)
unnamed: R120.2, TR1.21 (CT)
unnamed: R128.2, TR1.24 (CT)
unnamed: R141.1, U22.1
unnamed: R142.1, U20.1
unnamed: R143.1, U21.1
unnamed: C113.1, R132.2, R133.1, U1.1 (FB)
unnamed: L7.1, U1.6 (LX)
unnamed: C99.1, C100.2, C101.1, L5.2, R129.1, R130.2, U11.1 (+Vin)
unnamed: C100.1, C101.2, C102.2, L5.4, R129.2, R131.1, U11.2 (-Vin)
unnamed: R144.1, U11.5 (TRIM)

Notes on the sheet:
m.2 Standoffs for 2230, 2242, 2260 and 2280
SoC Power LED
SoC Activity LED
Pi CM4/CM5
M2.5 Standoffs for CM5
5V/5A System Supply
Mechanical Mounting Holes
m.2 Activity LED
3V3/3A for m.2 NVMe SSD

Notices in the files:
power/yanartas-pillowbox-power.kicad_pcb:
©2026 Jan Sebastian Götte cc-by-sa
